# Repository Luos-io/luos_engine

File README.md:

Version: 3.0.0

# Luos-engine: Empowering Developers

Luos-engine provides a simple and efficient way to manage your hardware products as a collection of independent software features. You can easily create and share these features with your team, external developers, or the wider community. Luos-engine is an open-source lightweight library that can be utilized on any microcontroller or computer, with any network, enabling free and fast development of multi-electronic-board connected products. Choosing Luos-engine for your product design empowers you to develop, debug, validate, monitor, and manage it from anywhere.

## Benefits for the Community

Many embedded developments start from scratch. By using Luos-engine, you can leverage the work already done by you, your company, or the Luos community. The reusability of features encapsulated in Luos-engine services accelerates the time it takes for your products to reach the market while ensuring the robustness and universality of your applications.

- Join the [Luos Discord server](http://discord.gg/luos) to connect with the community.

## Best Practices with Luos-engine

Luos-engine promotes organized and effective development practices, ensuring the scalability, flexibility, and adaptability of your product from the initial idea to maintaining an industrialized fleet.

## Let's do this​

- → Try on your own with the [get started](https://www.luos.io/tutorials/get-started)
- → Consult the full [documentation](https://www.luos.io/docs)

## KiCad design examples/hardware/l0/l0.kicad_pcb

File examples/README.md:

# Examples

In this section you will find multiple examples for multiple architectures and IDE.
The Apps forlder is dedicated to Applications service. Application services don't rely on any hardware so they are cross platform.

## Good practices with Luos​
Luos proposes organized and effective development practices, guaranteeing development flexibility and evolutivity of your hardware product, from the idea to the maintenance of the industrialized product fleet.
The examples follows some of those rules but not all of them because most of them are just components and not complete products.

## To learn more
This section details the features of Luos technology as an embedded development platform, following these subjects:

* Let's test through the [Luos get started](https://www.luos.io/tutorials/get-started), to build, flash, run, and control your very first Luos code.
* The [Basics of Luos](https://www.luos.io/docs/luos-technology/basics), explaining the general concepts and the project organization.
* Definition of [Nodes](https://www.luos.io/docs/luos-technology/node), and the relation between Luos and the physical world.
* Definition of [Packages](https://www.luos.io/docs/luos-technology/package), and how to make a portable and reusable development.
* Definition of [Services](https://www.luos.io/docs/luos-technology/services), how to create and declare features in your product.
* Definition of [Messages](https://www.luos.io/docs/luos-technology/message), when, why, and how to handle them, explaining the more advanced features of Luos.

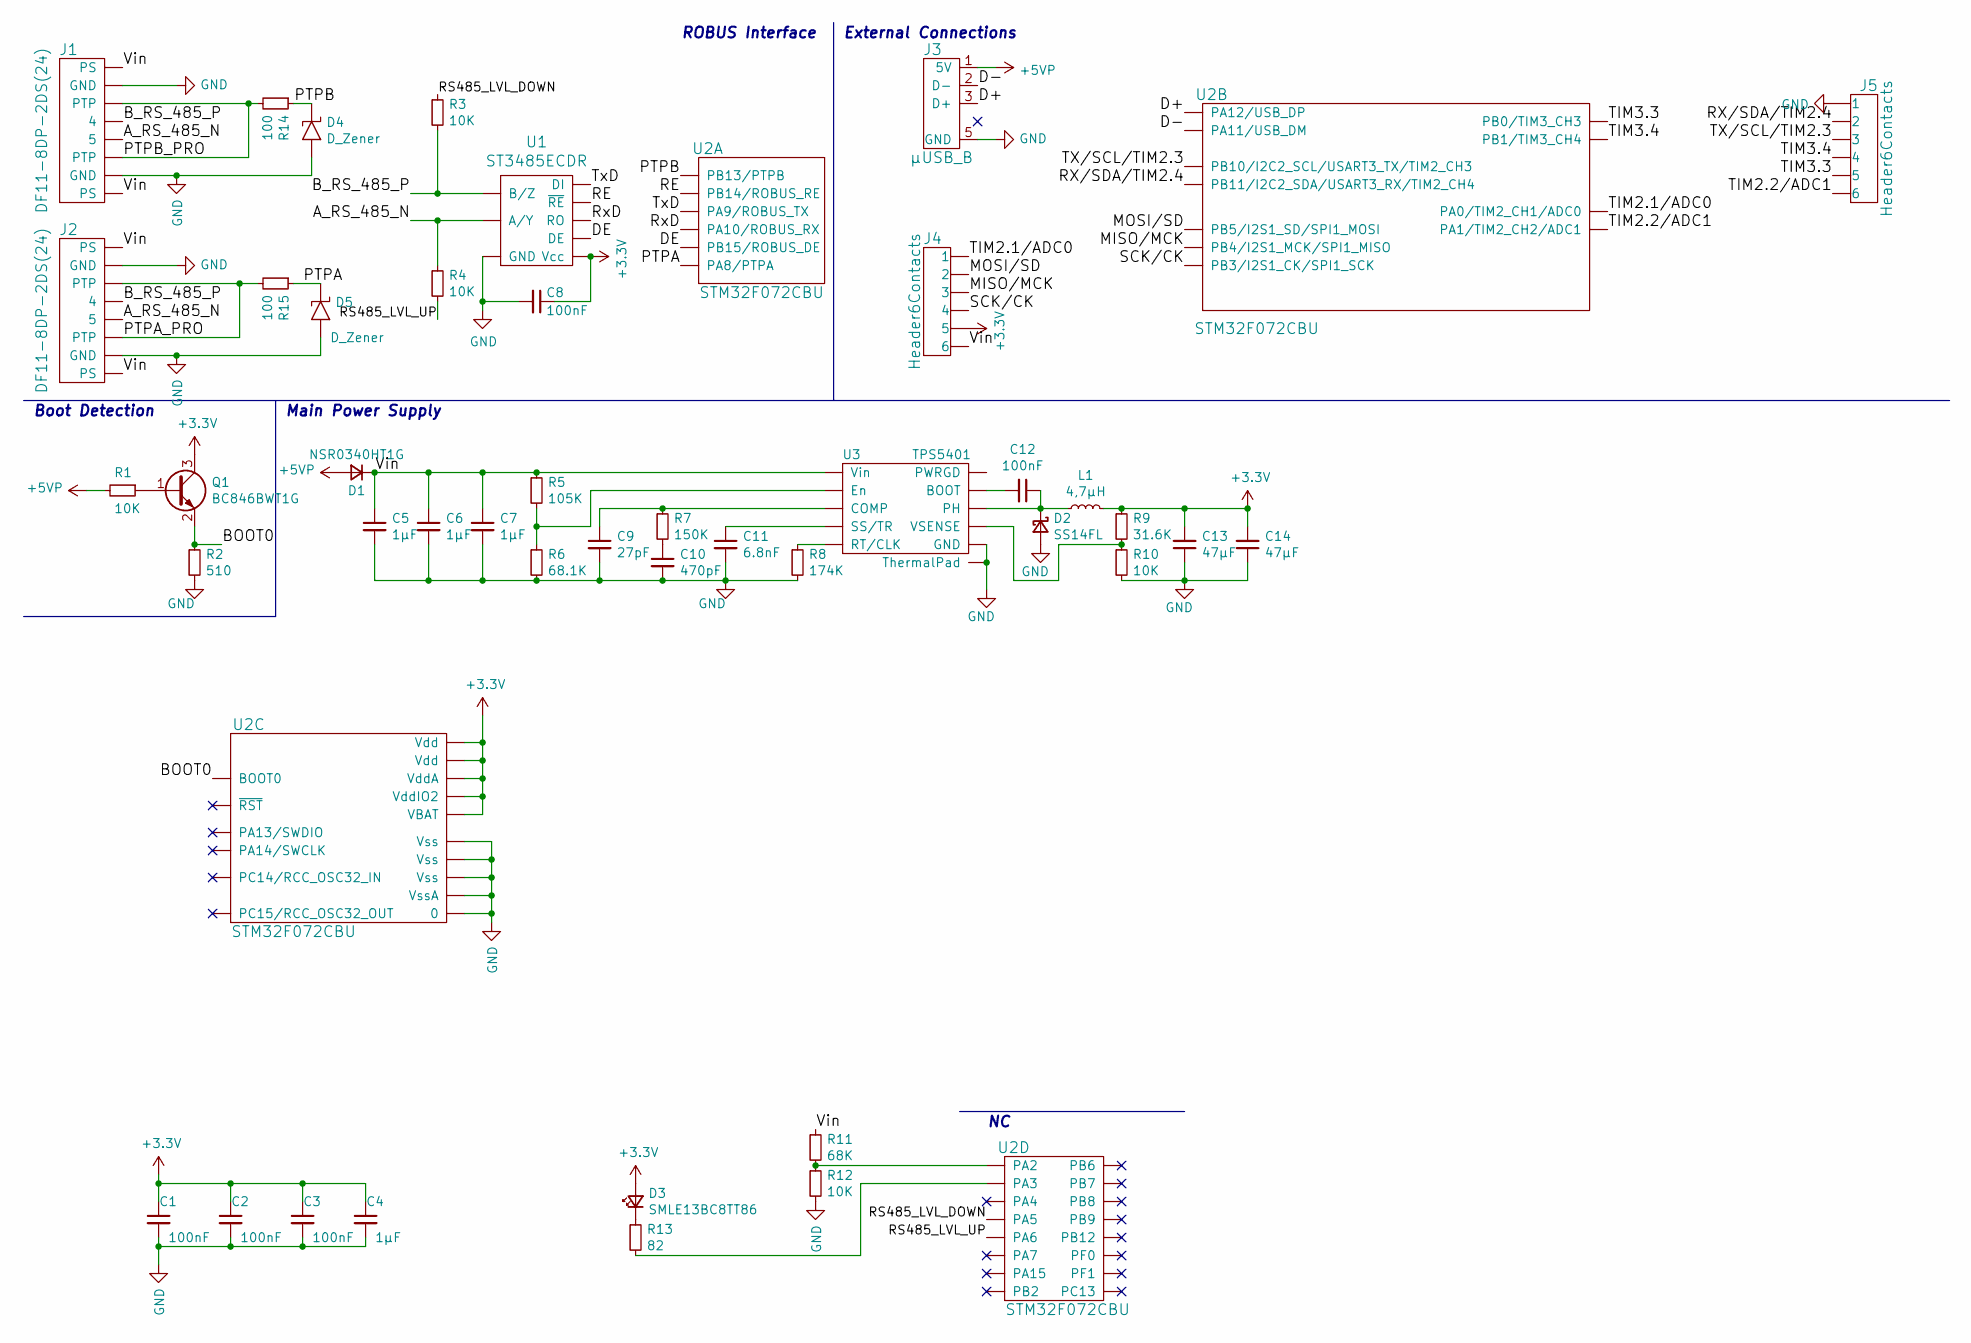
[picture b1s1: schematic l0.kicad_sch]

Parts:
C1, C2, C3, C8, C12: 100nF; C_0402_NoSilk
C4, C5, C6, C7: 1µF; C_0402_NoSilk
C9: 27pF; C_0402_NoSilk
C10: 470pF; C_0603
C11: 6.8nF; C_0603
C13, C14: 47µF; C_1206
D1: NSR0340HT1G; D_SOD-323F
D2: SS14FL; SOD-123F
D3: SMLE13BC8TT86; LED_0603
D4, D5: D_Zener; D_SOD-323F
J1, J2: DF11-8DP-2DS(24)
J3: µUSB_B; MicroUSB_B
J4, J5: Header6Contacts; 826926-6
L1: 4,7µH; L_0806
Q1: BC846BWT1G; SOT-323_SC-70
R1, R3, R4, R10, R12: 10K; R_0402_NoSilk
R2: 510; R_0402_NoSilk
R5: 105K; R_0402_NoSilk
R6: 68.1K; R_0402_NoSilk
R7: 150K; R_0402_NoSilk
R8: 174K; R_0402_NoSilk
R9: 31.6K; R_0402_NoSilk
R11: 68K; R_0402_NoSilk
R13: 82; R_0402_NoSilk
R14, R15: 100; R_0402_NoSilk
U1: ST3485ECDR; SO8
U2: STM32F072CBU; UFQFPN48
U3: TPS5401; S-PDSO-G10

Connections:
+3V3: C1.1, C2.1, C3.1, C4.1, C8.1, C13.2, C14.2, D3.2 (A), J4.5, L1.2, Q1.3 (C), R9.1, U1.8 (Vcc), U2.1 (VBAT), U2.9 (VddA), U2.24 (Vdd), U2.36 (VddIO2), U2.48 (Vdd)
+5VP: D1.2 (A), J3.1 (5V), R1.2
/A_RS_485_N: J1.5, J2.5, R4.1, U1.6 (A/Y)
/BOOT0: Q1.2 (E), R2.1, U2.44 (BOOT0)
/B_RS_485_P: J1.4, J2.4, R3.2, U1.7 (B/Z)
/D+: J3.3 (D+), U2.33 (PA12/USB_DP)
/D-: J3.2 (D-), U2.32 (PA11/USB_DM)
/DE: U1.3 (DE), U2.28 (PB15/ROBUS_DE)
/MISO/MCK: J4.3, U2.40 (PB4/I2S1_MCK/SPI1_MISO)
/MOSI/SD: J4.2, U2.41 (PB5/I2S1_SD/SPI1_MOSI)
/PTPA: D5.1 (K), R15.1, U2.29 (PA8/PTPA)
/PTPA_PRO: J2.3 (PTP), J2.6 (PTP), R15.2
/PTPB: D4.1 (K), R14.1, U2.26 (PB13/PTPB)
/PTPB_PRO: J1.3 (PTP), J1.6 (PTP), R14.2
/RE: U1.2 (~RE), U2.27 (PB14/ROBUS_RE)
/RS485_LVL_DOWN: R3.1, U2.15 (PA5)
/RS485_LVL_UP: R4.2, U2.16 (PA6)
/RX/SDA/TIM2.4: J5.2, U2.22 (PB11/I2C2_SDA/USART3_RX/TIM2_CH4)
/RxD: U1.1 (RO), U2.31 (PA10/ROBUS_RX)
/SCK/CK: J4.4, U2.39 (PB3/I2S1_CK/SPI1_SCK)
/TIM2.1/ADC0: J4.1, U2.10 (PA0/TIM2_CH1/ADC0)
/TIM2.2/ADC1: J5.6, U2.11 (PA1/TIM2_CH2/ADC1)
/TIM3.3: J5.5, U2.18 (PB0/TIM3_CH3)
/TIM3.4: J5.4, U2.19 (PB1/TIM3_CH4)
/TX/SCL/TIM2.3: J5.3, U2.21 (PB10/I2C2_SCL/USART3_TX/TIM2_CH3)
/TxD: U1.4 (DI), U2.30 (PA9/ROBUS_TX)
/Vin: C5.1, C6.1, C7.1, D1.1 (K), J1.1 (PS), J1.8 (PS), J2.1 (PS), J2.8 (PS), J4.6, R5.1, R11.1, U3.2 (Vin)
GND: C1.2, C2.2, C3.2, C4.2, C5.2, C6.2, C7.2, C8.2, C9.2, C10.2, C11.2, C13.1, C14.1, D2.2 (A), D4.2 (A), D5.2 (A), J1.2 (GND), J1.7 (GND), J2.2 (GND), J2.7 (GND), J3.5 (GND), J5.1, R2.2, R6.2, R8.2, R10.2, R12.2, U1.5 (GND), U2.0, U2.8 (VssA), U2.23 (Vss), U2.35 (Vss), U2.47 (Vss), U3.9 (GND), U3.11 (ThermalPad)
unnamed: C9.1, R7.1, U3.8 (COMP)
unnamed: C10.1, R7.2
unnamed: C11.1, U3.4 (SS/TR)
unnamed: C12.1, D2.1 (K), L1.1, U3.10 (PH)
unnamed: C12.2, U3.1 (BOOT)
unnamed: D3.1 (K), R13.1
unnamed: Q1.1 (B), R1.1
unnamed: R5.2, R6.1, U3.3 (En)
unnamed: R8.1, U3.5 (RT/CLK)
unnamed: R9.2, R10.1, U3.7 (VSENSE)
unnamed: R11.2, R12.1, U2.12 (PA2)
unnamed: R13.2, U2.13 (PA3)

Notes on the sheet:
Boot Detection
External Connections
Main Power Supply
ROBUS Interface

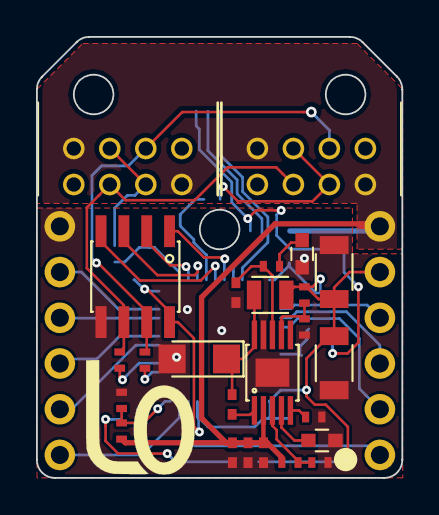
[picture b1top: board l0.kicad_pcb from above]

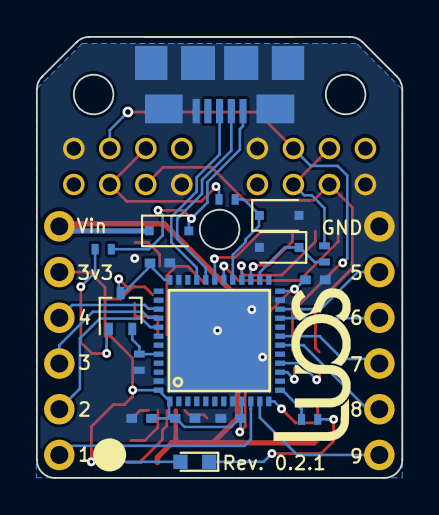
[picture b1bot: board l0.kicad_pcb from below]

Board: 2 copper layers, 20.3 x 24.5 mm, 44 parts (17 on the bottom side), 40 nets.

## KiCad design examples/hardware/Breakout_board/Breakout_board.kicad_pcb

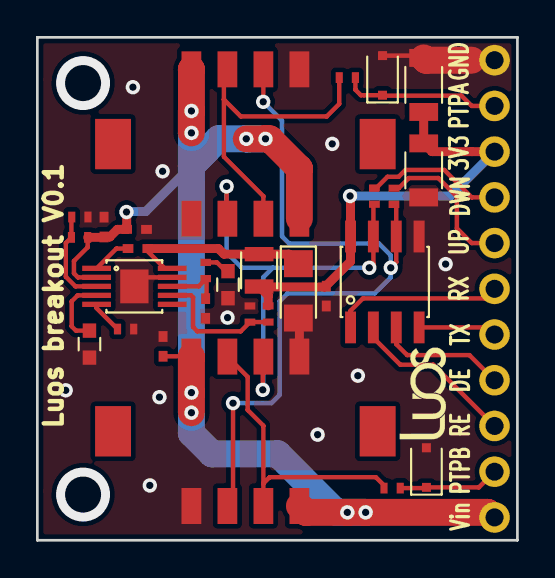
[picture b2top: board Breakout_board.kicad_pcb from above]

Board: 2 copper layers, 26.7 x 27.9 mm, 29 parts (0 on the bottom side), 23 nets.

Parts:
C1, C2, C3: 1µF; C_0402_NoSilk
C4: 27pF; C_0402_NoSilk
C5: 470pF; C_0603
C6: 6.8nF; C_0603
C7, C8: 100nF; C_0402_NoSilk
C9, C10: 47µF; C_1206
D2, D3: D_Zener; D_SOD-323F
D4: SS14FL; SOD-123F
J1, J2: DF11-8DP-2DS(24); DF11C-8DP-2V(57)
J3: Header11Contacts; 826926-11
L1: 4,7µH; L_0806
R1, R2: 100; R_0402_NoSilk
R3: 105K; R_0402_NoSilk
R4: 68.1K; R_0402_NoSilk
R5: 150K; R_0402_NoSilk
R6, R7, R10: 10K; R_0402_NoSilk
R8: 174K; R_0402_NoSilk
R9: 31.6K; R_0402_NoSilk
U1: ST3485ECDR; SO8
U2: TPS5401; S-PDSO-G10

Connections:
+3V3: C7.1, C9.2, C10.2, J3.9, L1.2, R9.1, U1.8
/A_RS_485_N: J1.5, J2.5, R7.1, U1.6
/B_RS_485_P: J1.4, J2.4, R6.2, U1.7
/DE: J3.4, U1.3
/PTPA: D3.1, J3.10, R2.1
/PTPA_PRO: J2.3, J2.6, R2.2
/PTPB: D2.1, J3.2, R1.1
/PTPB_PRO: J1.3, J1.6, R1.2
/RE: J3.3, U1.2
/RS485_LVL_DOWN: J3.8, R6.1
/RS485_LVL_UP: J3.7, R7.2
/RxD: J3.6, U1.1
/TxD: J3.5, U1.4
/Vin: C1.1, C2.1, C3.1, J1.1, J1.8, J2.1, J2.8, J3.1, R3.1, U2.2
GND: C1.2, C2.2, C3.2, C4.2, C5.2, C6.2, C7.2, C9.1, C10.1, D2.2, D3.2, D4.2, J1.2, J1.7, J2.2, J2.7, J3.11, R4.2, R8.2, R10.2, U1.5, U2.9, U2.11
unnamed: C4.1, R5.1, U2.8
unnamed: C5.1, R5.2
unnamed: C6.1, U2.4
unnamed: C8.1, D4.1, L1.1, U2.10
unnamed: C8.2, U2.1
unnamed: R3.2, R4.1, U2.3
unnamed: R8.1, U2.5
unnamed: R9.2, R10.1, U2.7

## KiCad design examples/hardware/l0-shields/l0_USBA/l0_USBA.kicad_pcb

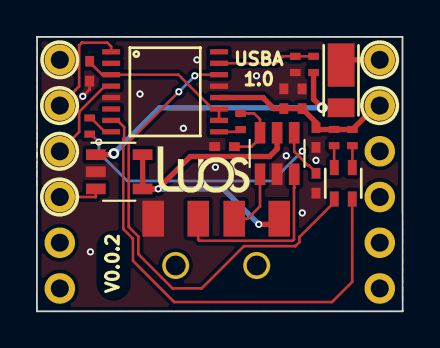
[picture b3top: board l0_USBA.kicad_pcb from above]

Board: 2 copper layers, 20.3 x 15.2 mm, 19 parts (0 on the bottom side), 20 nets.

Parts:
C1, C2: 47pF; C_0402_NoSilk
C3, C4, C5: 100nF; C_0402_NoSilk
C6: 4.7uF; C_0402_NoSilk
D1: KPTB-1615ESGC
D2: DFLS230L-7; PowerDI-123
J1: USB_A; USBA_SMD
J2: l0_Shield_Socket
R1, R2: 27; R_0402_NoSilk
R3: 4K7; R_0402_NoSilk
R4: 10K; R_0402_NoSilk
R5: 66,5; R_0402_NoSilk
R6: 56; R_0402_NoSilk
U1: FT230X; SSOP-16
U2: STMPS2171STR; SOT-23-5
U3: USBLC6-2SC6; SOT23-6L

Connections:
+3V3: C4.1, C5.1, C6.1, J2.5, R5.1, R6.1, U1.12
+5V: J1.1, U2.4, U2.5, U3.5
/RxD: J2.9, U1.4
/Rx_LED: D1.4, U1.7
/TxD: J2.8, U1.1
/Tx_LED: D1.2, U1.14
/Vin: D2.1, J2.6
GND: C1.2, C2.2, C3.2, C4.2, C5.2, C6.2, J1.4, J2.7, R4.1, U1.5, U1.13, U2.2, U3.2
unnamed: C1.1, R2.2, U3.6
unnamed: C2.1, R1.2, U3.4
unnamed: C3.1, U1.3, U1.10, U1.11
unnamed: D1.1, R5.2
unnamed: D1.3, R6.2
unnamed: J1.2, U3.1
unnamed: J1.3, U3.3
unnamed: J2.10, U2.3
unnamed: R1.1, U1.8
unnamed: R2.1, U1.9
unnamed: R3.1, R4.2, U1.15
VBUS: D2.2, R3.2, U2.1

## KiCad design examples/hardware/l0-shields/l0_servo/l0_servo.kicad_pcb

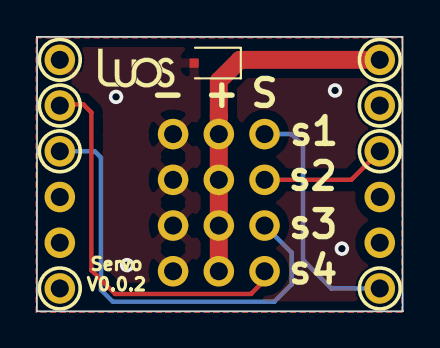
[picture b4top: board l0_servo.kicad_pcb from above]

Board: 2 copper layers, 20.3 x 15.2 mm, 6 parts (0 on the bottom side), 6 nets.

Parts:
D1: D_Zener; D_SOD-323F
J1: l0_Socket; l0_Shield_Socket
s1, s2, s3, s4: Header3Contacts; 826926-3

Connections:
GND: D1.2, J1.7, s1.3, s2.3, s3.3, s4.3
unnamed: J1.1, s1.1
unnamed: J1.4, s2.1
unnamed: J1.8, s4.1
unnamed: J1.9, s3.1
VCC: D1.1, J1.6, s1.2, s2.2, s3.2, s4.2

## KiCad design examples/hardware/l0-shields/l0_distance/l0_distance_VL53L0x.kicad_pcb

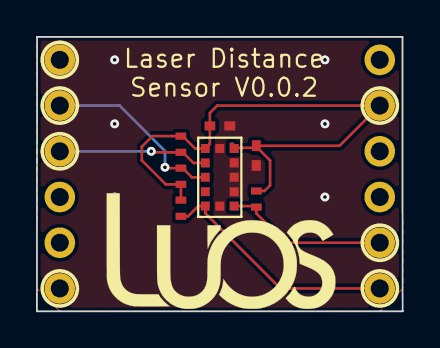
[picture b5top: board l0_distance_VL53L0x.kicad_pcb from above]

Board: 2 copper layers, 20.3 x 15.2 mm, 8 parts (0 on the bottom side), 6 nets.

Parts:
C1: 100nF; C_0402_NoSilk
C2: 4,7uF; C_0402_NoSilk
J1: l0_Socket; l0_Shield_Socket
R1, R2, R3, R4: 2K; R_0402_NoSilk
U1: VL53L0x

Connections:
+3V3: C1.1, C2.1, J1.5, R1.1, R2.1, R3.1, R4.1, U1.1, U1.11
/INT: J1.1, R3.2, U1.7
/SCL: J1.9, R1.2, U1.10
/SDA: J1.8, R2.2, U1.9
/SHUTDOWN: J1.2, R4.2, U1.5
GND: C1.2, C2.2, J1.7, U1.2, U1.3, U1.4, U1.6, U1.12

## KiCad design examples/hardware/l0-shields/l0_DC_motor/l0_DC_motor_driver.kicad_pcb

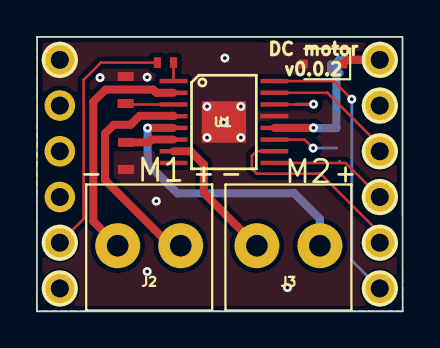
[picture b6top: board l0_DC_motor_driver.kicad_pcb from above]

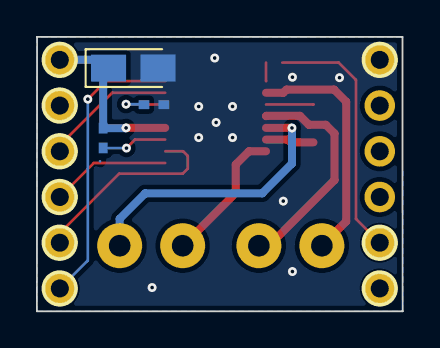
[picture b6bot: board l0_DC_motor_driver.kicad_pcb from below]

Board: 2 copper layers, 20.3 x 15.2 mm, 11 parts (3 on the bottom side), 17 nets.

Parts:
C1: 10µF; CP_Tantalum_Case-S_EIA-3216-12_Reflow
C2: 10nF; C_0402_NoSilk
C3: 2,2µF; C_0402_NoSilk
D1: D_Zener; D_SOD-323F
J1: l0_Shield_Socket
J2, J3: 1776275-2
R1: 20k; R_0402_NoSilk
R2, R3: 300m; R_0603
U1: DRV8833; HTSSOP-16

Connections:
/NC_PWM1: J1.1, U1.16
/NC_PWM2: J1.3, U1.9
/NO_PWM1: J1.4, U1.15
/NO_PWM2: J1.2, U1.10
/Robus_PS: C1.1, C2.1, D1.1, J1.6, U1.12
/~nFAULT: J1.12, U1.8
/~nSLEEP: J1.11, R1.2
GND: C1.2, C3.2, D1.2, J1.7, R2.2, R3.2, U1.13
unnamed: C2.2, U1.11
unnamed: C3.1, U1.14
unnamed: J2.1, U1.2
unnamed: J2.2, U1.4
unnamed: J3.1, U1.7
unnamed: J3.2, U1.5
unnamed: R1.1, U1.1
unnamed: R2.1, U1.6
unnamed: R3.1, U1.3

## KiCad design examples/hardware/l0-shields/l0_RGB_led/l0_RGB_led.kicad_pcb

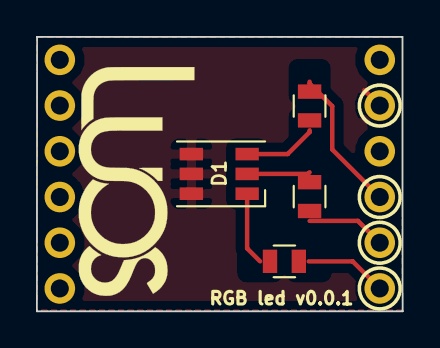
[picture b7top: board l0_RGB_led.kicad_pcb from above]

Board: 2 copper layers, 20.3 x 15.2 mm, 5 parts (0 on the bottom side), 7 nets.

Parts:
D1: LED_RGB; LED_RGB_PLCC-6
J1: l0_Socket; l0_Shield_Socket
R1, R2: 24; R_0805
R3: 68; R_0805

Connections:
+3V3: D1.4, D1.5, D1.6, J1.5
unnamed: D1.1, R3.2
unnamed: D1.2, R2.2
unnamed: D1.3, R1.2
unnamed: J1.1, R3.1
unnamed: J1.2, R2.1
unnamed: J1.3, R1.1

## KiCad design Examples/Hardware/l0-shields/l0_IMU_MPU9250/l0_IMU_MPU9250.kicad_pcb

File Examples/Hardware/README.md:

# Electronics basis

This folder contains hardwares librairies used by Luos to inspire you to create your own designs:
 - **L0**: The base board used by Luos for demonstrastion purpose.
 - **l0-shields**: Different shields that can be used directly on the Luos L0 board for added functionality.
 - **STm32f0_disco_luos_shield**: a debugging shield equivalent to an L0 for STM32F072B-DISCO dev board.
 - **Breakout_board**: a small add-on board to make any board compatible with Luos L0.
 - **wiring_and_power**: a set of projects for Luos L0 compatible wires and power input boards.
 - **00_Common_Libraries**: a set of Kicad libraries commonly used.

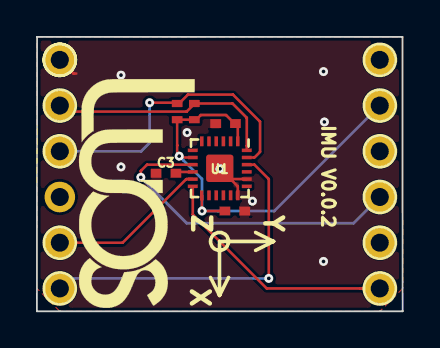
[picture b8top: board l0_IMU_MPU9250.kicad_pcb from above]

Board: 2 copper layers, 20.3 x 15.2 mm, 7 parts (0 on the bottom side), 9 nets.

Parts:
C1, C3: 100nF; C_0402_NoSilk
C2: 10nF; C_0402_NoSilk
J1: l0_Socket; l0_Shield_Socket
R1, R2: 4.7K; R_0402_NoSilk
U1: MPU-9250; MPU9250

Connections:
+3V3: C1.1, C2.1, J1.5, R1.1, R2.1, U1.1, U1.8, U1.13
/AD0_SD0: J1.3, U1.9
/FSYNC: J1.11, U1.11
/INT: J1.1, U1.12
/SCL: J1.9, R1.2, U1.23
/SDA: J1.8, R2.2, U1.24
/~CS: J1.12, U1.22
GND: C1.2, C2.2, C3.2, J1.7, U1.18, U1.20
unnamed: C3.1, U1.10

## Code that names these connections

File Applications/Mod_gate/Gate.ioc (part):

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Mcu.Name=STM32F072C(8-B)Ux
Mcu.Package=UFQFPN48
Mcu.UserName=STM32F072CBUx
PA10.GPIOParameters=GPIO_PuPd,GPIO_Label
PA10.GPIO_Label=ROBUS_RX
PA10.GPIO_PuPd=GPIO_PULLUP
PA10.Mode=Asynchronous
PA10.Signal=USART1_RX
PA2.GPIOParameters=GPIO_Label
PA2.GPIO_Label=ROBUS_POWER_SENSOR
PA2.Mode=IN2
PA2.Signal=ADC_IN2
PA3.GPIOParameters=GPIO_Label
PA3.GPIO_Label=LED
PA3.Signal=GPIO_Output
PA5.GPIOParameters=PinState,GPIO_PuPd,GPIO_Label
PA5.GPIO_Label=RS485_LVL_DOWN
PA5.GPIO_PuPd=GPIO_PULLUP
PA5.PinState=GPIO_PIN_RESET
PA5.Signal=GPIO_Output
PA6.GPIOParameters=PinState,GPIO_PuPd,GPIO_Label
PA6.GPIO_Label=RS485_LVL_UP
PA6.GPIO_PuPd=GPIO_PULLDOWN
PA6.PinState=GPIO_PIN_SET
PA6.Signal=GPIO_Output
PA8.GPIOParameters=GPIO_PuPd,GPIO_Label,GPIO_ModeDefaultEXTI
PA8.GPIO_Label=ROBUS_PTPA
PA8.GPIO_ModeDefaultEXTI=GPIO_MODE_IT_FALLING
PA8.GPIO_PuPd=GPIO_PULLUP
PA8.Signal=SharedStack_PA8
PA8.Stacked=true
PA9.GPIOParameters=GPIO_PuPd,GPIO_Label
PA9.GPIO_Label=ROBUS_TX
PA9.GPIO_PuPd=GPIO_PULLUP
PA9.Mode=Asynchronous
PA9.Signal=USART1_TX
PB10.GPIOParameters=GPIO_Label
PB10.GPIO_Label=TX
PB10.Mode=Asynchronous
PB10.Signal=USART3_TX
PB11.GPIOParameters=GPIO_Label
PB11.GPIO_Label=RX
PB11.Mode=Asynchronous
PB11.Signal=USART3_RX
PB13.GPIOParameters=GPIO_PuPd,GPIO_Label,GPIO_ModeDefaultEXTI
PB13.GPIO_Label=ROBUS_PTPB
PB13.GPIO_ModeDefaultEXTI=GPIO_MODE_IT_FALLING
PB13.GPIO_PuPd=GPIO_PULLUP
PB13.Signal=SharedStack_PB13
PB13.Stacked=true
PB14.GPIOParameters=GPIO_Label
PB14.GPIO_Label=ROBUS_RE
PB14.Signal=GPIO_Output
PB15.GPIOParameters=GPIO_Label
PB15.GPIO_Label=ROBUS_DE
PB15.Signal=GPIO_Output
RCC.SYSCLKFreq_VALUE=48000000
RCC.SYSCLKSource=RCC_SYSCLKSOURCE_PLLCLK
board=custom

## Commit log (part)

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2023-03-28 [Gate] Add an optional GATE_REFRESH_TIME_S configuration disabling the refresh rate auto-scaling.
    fix Gate timing
2023-03-28 Add thread locks macro avoiding data-race with HAL threads.
2023-03-28 [Native] Clean the led code
2023-03-28 [Native] Remove the button package from Gate_wscom example
2023-03-28 Add sanity assert
2023-03-28 Add thread locks macro avoiding data-race with polling services threads.
2023-03-28 Fix assert macro
2023-03-28 Add native broker option to setup IP and port of the server.
2023-03-28 Download mongoose only one time even if it's used by multiple libs.
2023-03-28 Create a PingPong game example
2023-03-28 multi-threading + a lot of improvement and fun
2023-03-28 Docker implmentation
2023-03-28 Create a separate thread for gaph
2023-03-28 Gaphism improvement
2023-03-28 final improvement of controls, displays, and readme
2023-03-28 Remove unused _WEAKED symbol
2023-03-31 Prevent streaming asserts on windows
2023-03-31 increase timeout for failed detection on windows
2023-03-31 Boost buffers for windows
2023-03-31 Link projects to platformio registry
2023-04-01 Update revisions
2023-04-02 Update to version 3.0.0 for local dev
2023-06-18 [Native] Do not lock the program execution if there is no broker running.
2023-06-19 Fix main lib library.json
2023-09-18 Clean luos_engine.h and remove unused `Luos_SetExternId`
2023-09-18 Rename and move the robus `config.h` file into `robus_config.h`
2023-09-18 Add the IO folder and source compilation.
2023-09-18 Move msg_alloc from Robus to IO
2023-09-18 Move public timestamp functions into public Luos_engine.h
2023-09-18 Remove useless node_state_t struct
2023-09-18 Move struct and configurations from Robus to IO
2023-09-18 Add an error in case of inclusion of luos.h
2023-09-18 Move general_stats_t from luos_engine.h to service_structs.h
2023-09-18 Remove dynamic baudrate management
2023-09-18 Group all node functions on a node.c.h
2023-09-18 Reshape reception and almost completely shortcut msg_tasks
2023-09-18 Fix timestamp msg reception computation
2023-09-18 Add streaming unit test
2023-09-18 Manage phy instantiation
2023-09-18 Improve luos_engine unit test
2023-09-18 Remove filters disableabilty and verbose mode.
    We will have to completely redesign them and they represent complexity when it come to move things.
2023-09-18 Assert if buffer full only on RX. TX can wait to load the buffer again...
2023-09-18 Remove unused Luos_SetFilterState function
2023-09-18 Move back rx and tx init into robus
2023-09-18 Improve UNIT_TEST_RUN macro to correctly manage function name passing to unity.
2023-09-18 Move robus init and loop things into IO
2023-09-18 Remove all context usage on msg_alloc
2023-09-18 Group all filter functions in a filter file
2023-09-18 Move topology management to LuosIO
2023-09-18 Create Service files
2023-09-18 Create a phy.h/c files defining phy structs
2023-09-18 Remove the redundant ll_service_number from robus context
2023-09-18 Exclude some test for windows because it fail to execute it
2023-09-18 RX CRC optimization
2023-09-18 [Gate] Add a small check if a service is excluded during detection.
2023-09-18 Fix addressing generation at detection start.
2023-09-18 Fix data dropping occurring during re-init
2023-09-18 Improve pub_sub unit tests
2023-09-18 Improve routing table unit tests
2023-09-18 Add service unit test
2023-09-18 Do not allow RX dropping during reception
2023-09-18 Move ll_service_t into Service_t, only one struct remain now.
2023-09-18 Remove useless main.h Od tests files
2023-09-18 Remove useless baudrate variable
2023-09-18 Enable test coverage report
2023-09-18 Modify master detection to be non-blocking. This allows networks to manage reception and send in loop.
2023-09-18 Rename `bootloader_core` into `luos_bootloader`
2023-09-18 Secure job and alloc slot management from dataraces and reduce IRQ off time
2023-09-18 Secure Pipe using Serial for STM32G4 clock configuration
2023-09-18 OK serial test with Native gate and L0 button
2023-09-18 Optimize freeRTOS example to fit in RAM
2023-09-18 Fix some typo
2023-09-18 !fix corrupted messages
2023-09-18 Secure job removal
2023-09-18 Fix phy_data protection
2023-09-18 Move data_ptr in alloc if there is no space for at least a header.
2023-09-18 Improve Robus configuration flags naming
2023-09-18 OK serial test with Native gate and STM32F4 button
2023-09-18 Fix a memory leak in case of dead target
2023-09-18 OK serial test with native gate and G474 and G431 button
2023-09-18 Minor code cleanup.
2023-09-18 Avoid assert in case of corrupted message reception. Properly trash it.
2023-09-18 Modify aloc slots management avoiding pointer movement and limiting IRQ disabling.
2023-09-18 OK serial test with Native gate and Arduino button and led, fix #440
2023-09-18 Clear auto-refresh when we clear service IDs.
2023-09-18 Create a serial_network
2023-09-18 Fix the detection flag init
2023-09-18 [OD] rename the `_private` var into `raw` to explicitely allow users to perform calculations with `raw` instead of converting it each time.
2023-09-18 Enable multi-phy capabilities
2023-09-18 Secure Robus initialization by setting Callback before enabling the hardware. This avoid a potential IRQ to broke the code.
2023-09-18 [SERIAL] Secure messy RX interpretation
2023-09-18 Improve ST Serial reception by removing RX IRQ and improve function naming
2023-09-18 Allow synchronized nodes to manage timestamping without any differential computation, fix #444
2023-09-18 Make a clean BAUDRATE configuration for networks
2023-09-18 Improve native timestamping precision
2023-09-18 Secure potential RX segfault if the RX buffer is smaller than the receiving datas.
2023-09-18 Fix a small datarace on RX
2023-09-18 Fix Gate compilation on windows
2023-09-18 !fix multi-phy
2023-09-18 Add a print for native assert
2023-09-18 Fix a typo
2023-09-18 Remove some useless reset on detetion and increase some timing allowing native to always perform as expected.
2023-09-18 Fix some code format
2023-09-18 Add a trace print on Gate segfault to catch it one day perhaps.
2023-09-18 Improve C++ compatibility by making it natively compilable in a C++ env
2023-09-18 Fix some OD warnings on `Controller_motor` example
2023-09-18 Remove networks from coverage, networks are very difficult to unit test, they are to close from hardware.
2023-09-18 Fix format
2023-09-18 Remove Inspector because we don't maintain it anymore.
2023-09-19 [SERIAL] Fix big message reception sizing and timing issue
2023-09-21 Make Luos_engine immune to port (PTP) glitch out of detection
2023-09-22 Improve header validation to avoid concurent ACK during detection
2023-09-22 Fix topology bug involving multiple networks with multiple ports
2023-09-25 Fix serial detection from RT compute unit
2023-09-25 Fix ACK collision during detection on ACK compatible phys
2023-09-26 Enable multiple phy on nodes other than detection
2023-09-28 Fix phy unit test
2023-09-28 Fix a cornercase where IRQ may stay stuck disabled
2023-11-06 Fix a data-race on Robus when we send something too close to the end of a reception.
2023-11-06 Update some hardware project to the new Kicad version
2023-11-06 use the value of the rx_phy_filter to know if we compute it or not
2023-11-07 [Gate] Secure Bootloader JSON management
2023-11-07 [Gate] manage multiple JSON reception and treatment.
2023-11-07 Fix unit test to match new nodes index computation
2023-11-07 Fix some comment typo
2023-11-07 Fix node indexes computation in case of a phy with multiple branches.
2023-11-07 Improve general readme
2023-11-07 Improve Bootloader node_config to be more compliant and light
2023-11-07 [GATE] Fix target_trans_position to get raw value instead of converting it from mm. This allow to get the returned value in m as well as the target.
2023-11-07 Fix service indexes computation
2023-11-20 Switch license from Apache 2 to MIT
2023-11-22 Add a source filtering allowing to check message known provenance, fix #451
2023-11-22 Adapt tests
2023-12-08 Remove the newboot linker script config
2023-12-13 Fix the number of allocated phy assertion
2023-12-21 Consider local services as trusted and do not exclude them if someone is asking us to. Service still removed from the routing table and auto-update still canceled.
2024-01-03 [Gate] Allow to receive and manage someone excluding the Gate
2024-01-03 Add a Luos_ReadFromCmd function to Luos_engine
2024-01-05 Revert "Temporarily remove the ESP build on GH, #423"
    This reverts commit f00e3e64d243d0497197019c3c5a24d49d8489f8.
2024-01-22 Native examples now use WebSockets instead of Robus
2024-01-22 Move broker scripts into Pyluos as command lines
2024-01-22 add an Arduino HAL tested on mkr1000
2024-01-22 [Network/WS/HAL/Native] Websocket configuration can now be override through environment variable
2024-01-22 Fix some broken links on Readme
2024-01-22 fix a WebSocket configuration typo
2024-01-22 Auto-update are for services not nodes, fix #465
2024-01-24 Create serial_network STM32L474 HAL
2024-01-24 Fix a small luos_engine compilation display
2024-01-29 [Gate] Allow user to add custom messages management to tiny-json converter
2024-01-29 Add a custom pyluos type management example
2024-01-29 Add a custom Gate example
2024-01-29 Improve some readme
2024-02-01 Enable shared libs compilation by compiling directly the lib
2024-02-02 ensure that PTP is low after reset
2024-02-12 add -fpic flag
2024-02-15 [product] Add a demo notebook
2024-02-15 [product] Improve readme with video and link to doc.
2024-02-15 [product] fix a broken link on Readme
2024-02-15 [product] First working galvo
2024-02-22 Update Luos_engine HAL script
2024-02-22 Expose packages functions
2024-02-22 WS HAL for BROWSER move to CPP
2024-02-22 Remove useless luos_engine shared lib compilation in the end.
2024-02-22 Manage websocket in wasm
2024-02-22 Add a small HTML to the led example on browser
2024-02-22 Update the browser led Readme
2024-03-07 use job msg size instead of header msg size when reading message from service
2024-03-22 [Gate] Remove the wait period of the Gate
2024-03-22 [Gate] Remove auto-updates before setting a new one allowing to keep only one at a time per services.
2024-03-22 Fix services auto-update by allowing to be removed by sending 0 as period.
2024-03-22 [Pipe] remove a useless variable on the serial TX protocol.
2024-03-22 If a service ask a new update overwrite the update time of the existing one.
2024-03-22 [Gate] completely remove tempos
2024-03-22 [Gate] remove unused polling mode of the Gate
2024-03-22 [Gate] Switch gate into an event based management
2024-03-22 [Pipe] Increase default serial baudrate to 3000000 Baud
2025-01-23 loop while serial device not connected
2026-04-27 test(python): ctypes smoke — dylib loads and cmult roundtrips
2026-04-27 feat(python): add bindings/python/.gitignore (force-add past root ignore rule)
2026-04-27 test(python): blinker end-to-end handler-level alternation
2026-04-27 feat(shared_lib): finalize native_lib env and expose cmult smoke test
    Consolidates the three WIP commits:
    - Add cmult() with visibility("default") as an exported smoke-test symbol
    - Switch platformio default env to native_lib
    - Iterate shared_lib_build.py (network archive discovery, LINKFLAGS)
2026-04-27 feat(python): Message view with lazy header unpack
2026-04-27 feat(python): add dylib discovery with env var overrides
2026-06-02 feat(python): add platform-key helper for phy binary selection
2026-06-02 ci(python): build platform wheels and publish phy assets on release
    Wheels bundle libluos_engine.* via the package data; phy dylibs and a
    per-platform sha256 manifest are attached to the GitHub Release. A
    post-publish job installs the wheel and runs the network blinker,
    proving the phy download path end-to-end.
2026-06-02 feat(python): add engine version module (CI overwrites at build)
